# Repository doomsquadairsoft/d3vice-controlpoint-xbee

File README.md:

# d3vice-controlpoint-xbee
Arduino Fio / XBee based D3VICE control point for Airsoft games

## Feedback

If you have used and enjoy this code base, I'd love to hear from you!

## Development setup process

  * Download, Install [Atom editor](https://atom.io)
  * Download, Install [Platformio](https://platformio.org/install/ide?install=atom) Atom package
  * Restart atom. Open Atom & PlatformIO then import this repo.

??? @TODO once I figure out the process after this
  * Install contributed libraries `Sketch > Include Libraries > Manage Libraries`
    * Adafruit NeoPixel library
    * XBee-Arduino library
  * Add your user account to tty and dialout groups (May or may not be required for your OS)
    * `sudo usermod -aG tty,dialout <YOUR_USERNAME_HERE>`

## Enclosure Ideas

  * [MTM Survivor Dry Box with O-Ring Seal, Large](https://www.amazon.com/MTM-Survivor-Ring-Orange-Large/dp/B002KENWZY/ref=pd_rhf_ee_s_cp_0_3?_encoding=UTF8&pd_rd_i=B002KENWZY&pd_rd_r=DREY47809SR4JA75TENW&pd_rd_w=tL9qp&pd_rd_wg=YghNF&psc=1&refRID=DREY47809SR4JA75TENW)
  * [Seahorse SE-300 Protective Case Without Foam](https://www.amazon.com/Seahorse-Protective-Case-without-Orange/dp/B001A1TR1Q/ref=sr_1_14?ie=UTF8&qid=1509563510&sr=8-14&keywords=waterproof+case)

## XBee

### Setup

To connect to the XBee, a [SparkFun FTDI Basic Breakout 3.3v](https://www.sparkfun.com/products/9873) is used along with an [Adafruit XBee Adapter kit v1.1](https://www.adafruit.com/product/126). As my Adafruit XBee adapter kit v1.1 is discontinued, the replacment seems to be Adafruit's [USB XBee Adapter](https://www.adafruit.com/product/247) which I haven't tested but should do the trick. A separate FTDI chip isn't necessary with that new model.

XCTU is the program for configuring XBee modules. It is cross-platform.

57600 baudrate

Set the controlpoint as an ZB Router API NOT a ZB Endpoint API! Endpoint will work, but has complications with sleep mode.

#### XCTU Troubleshootinghttps://www.youtube.com/watch?v=ChCHfJoo9CQ

Make sure if using it on linux, you add yourself to the `dialout` group. Example: `sudo usermod -a -G dialout chris`

Make sure Arduino IDE is closed when working with XCTU. Radio discovery can be finnicky, but it works when it works.

XCTU's download links on Digi's website are usually broken. Find the filename from the [download page](https://www.digi.com/products/xbee-rf-solutions/xctu-software/xctu#productsupport-drivers), then manually browse their [ftp server](ftp://ftp1.digi.com/support/utilities/) for the correct version of XCTU.

If you can't get XCTU to communicate with your XBee, the rule of thumb is keep trying. It doesn't always work the first or second time. Try the different connection methods as well, from discovery to manually entering XBee serial/USB configuration.

### Power

The XBee is very sensitive when it comes to power. It needs as close to 3.3V as possible. When using USB, the Fio gives it a clean 3.285V. 3.296 was acheived using the buck converter regulator and that seemed to do the trick. If you are attempting to remotely program the XBee using X-CTU, and the read process seems slow, it may be that the XBee is crashing when it tries to pull power. Check voltages and try again.

### IDs

#### PAN ID

0x73706F6B616E6561 (ASCII spokanea)

#### switzerland-robust

SH 0013A200
SL 40B51A26

#### borders-portals

SH 0013A200
SL 40B774EC

## Special Thanks

The following people have helped this project in some way, and deserve a mention. Thank you all for helping this project become a reality!

  * [BulldogLowell](https://forum.arduino.cc/index.php?action=profile;u=258955) for helping me with code when I got stuck
  * [gfvalvo](https://forum.arduino.cc/index.php?action=profile;u=557197) for helping me with code when I got stuck
  * [Jiggy-Ninja](https://forum.arduino.cc/index.php?action=profile;u=53253) a.k.a. [MarkRD](https://hackaday.io/MarkRD) for helping me with code when I got stuck

## Todo list

  * [x] Fix phase 3 issue where ttw is ???
  * [ ] Implement XBee
  * [ ] Implement debugging via XBee wireless link
  * [x] Fix button debounce issue
  * [x] Fix endless beep on phase >=1
  * [x] Add button hold logic
  * [x] Implement ButtonManager
  * [ ] Try LoRa radio [Moteino](https://lowpowerlab.com/shop/product/119) looks nice.

## Parts list

  * (2) 220 Ohm resistor (JP3 button LEDs) DEPRECATED -- The buttons have their own capacitor
  * (3) 10K Ohm resistor (x2 JP4 button switches, x1 Battery Voltage Divider)
  * (1) 100K Ohm resistor (Battery voltage divider)
  * (1) 470 Ohm resistor (R1 Level shifter)
  * (1) 100 Ohm resistor (R2 buzzer)
  * (1) [Arduino Fio](https://amzn.to/2vkoAoj)
  * (1) 900MHz series XBee S2B
  * (1) [Digi JF1R6-CR3-4I U.FL fem to RPSMA fem cable](https://www.mouser.com/productdetail/digi-international/jf1r6-cr3-4i?qs=YPg7lQ8MWSd%252bJ21AYb5tjA%3D%3D)
  * (1) [2.4GHz dipole antenna](https://www.mouser.com/ProductDetail/Laird-LS-Research/001-0001?qs=%2fha2pyFaduic7%252bgB%2fLd2y%2fydYaVrig4l0IiQcO85%252biN2Plogftrjhg%3d%3d) (@TODO this doesn't seem right)
  * (1) 5V Buzzer
  * (1) 1000 uF electrolytic capacitor
  * (1) [TI 74AHCT125](http://adafru.it/1787) (NeoPixel 3V to 5V level shifter)
  * (1) [Red Arcade pushbutton](https://amzn.to/2qzc0vI)
  * (1) [Blue Arcade pushbutton](https://amzn.to/2vszEjp)
  * (2) [18650 Cell holder](https://amzn.to/2JN0Lsh)
  * (2) 18650 Li-Ion 3.7V battery
  * (1) [Qunqi MP1584EN DC-DC Buck Converter](https://amzn.to/2EPh9oB)
    * (1) [Alternative Power supply 001](https://www.ebay.com/itm/Durable-Quality-DC-DC-12V-To-3-3V-5V-Buck-Step-down-Power-Supply-Module-RH/113014911452?hash=item1a5036b1dc:g:4ecAAOSwzWpZjrM5)
  * (1) [MTM Survivor Dry Box with O-Ring](https://amzn.to/2JQuaSx)
  * (1) [Medium keyswitch](https://www.sparkfun.com/products/retired/11473)
  * (n) [24 AWG copper wire](https://amzn.to/2FrzB6S)
  * (2) [Chasis handles](https://www.mouser.com/ProductDetail/RAF-Electronic-Hardware/8075-440-A-24?qs=%2fha2pyFadugv9UkFwjFj1mse%2fGe0gQVLL5igE44%2fsfXi69vVZQTh6A%3d%3d)
  * (?) [4-40 bolts](https://www.banggood.com/4-40-UNC-Stainless-Steel-Hex-Socket-Head-Cap-Screws-Nuts-Assortment-Kit-126pcs-p-1147256.html?rmmds=search&cur_warehouse=CN)
  * (?) [LED Strip Housing](https://www.ebay.com/itm/50cm-U-V-YW-Aluminium-Housing-Holder-For-LED-Strip-Light-Bar-Under-Cabinet-Lamp/372358319157?hash=item56b2490c35:m:mi8XunysgHwlc1OMXDJ0slw:rk:29:pf:0)
  * (2) [Arcade Button Quick-Connect Wire Pairs - 0.11"](https://www.adafruit.com/product/1152)

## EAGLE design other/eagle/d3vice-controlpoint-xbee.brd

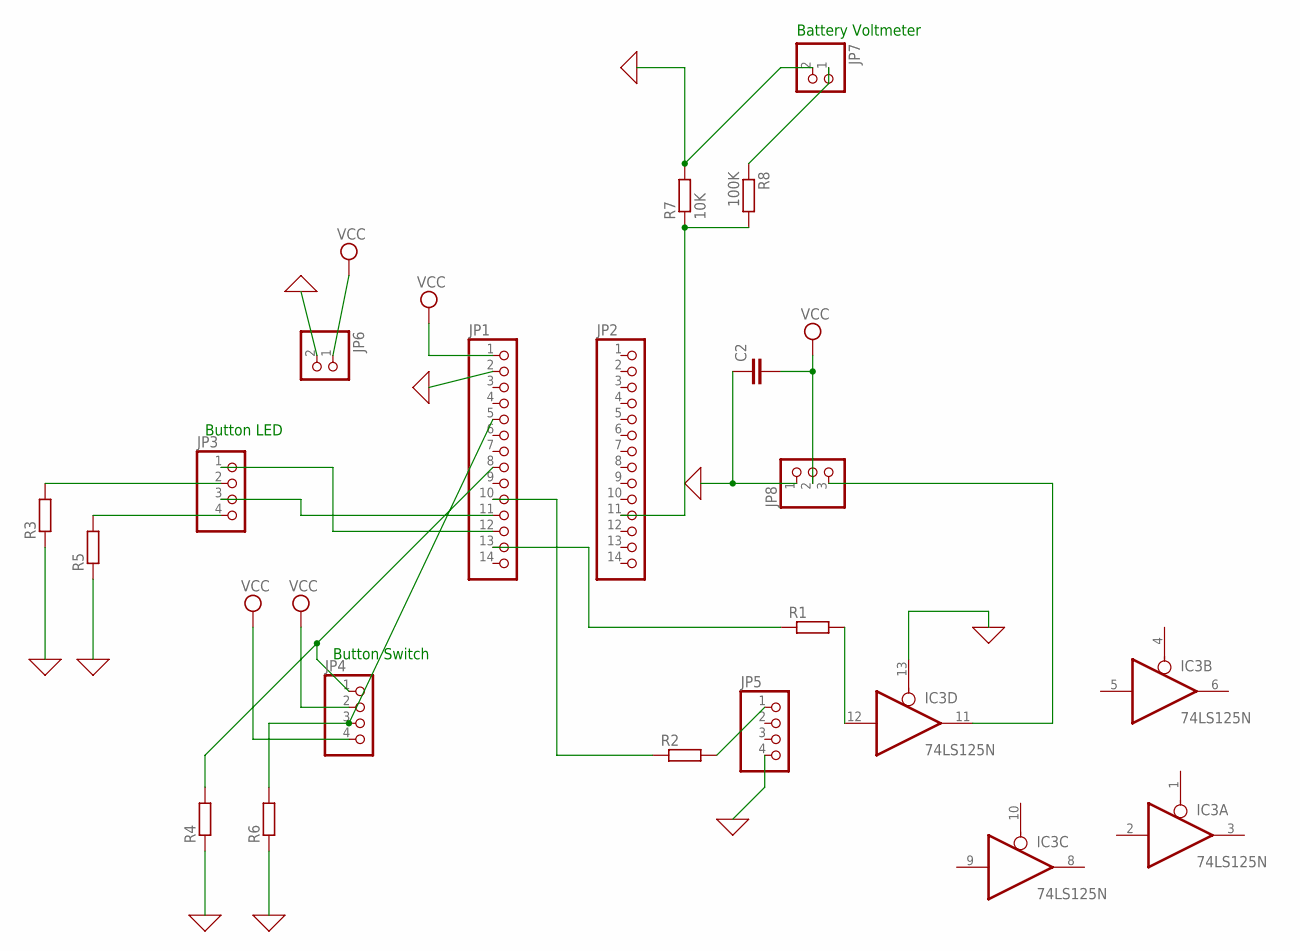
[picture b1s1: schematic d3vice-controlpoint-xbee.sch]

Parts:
C2: C-EU050-045X075; C050-045X075
IC3: 74LS125N; DIL14
JP1, JP2: PINHD-1X14; 1X14
JP3, JP4, JP5: PINHD-1X4; 1X04
JP6, JP7: PINHD-1X2; 1X02
JP8: PINHD-1X3; 1X03
R1, R2, R3, R4, R5, R6: R0204/7; 0204/7
R7: 10K; 0204/7
R8: 100K; 0204/7

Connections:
0: JP7.2, R7.2
GND: C2.1, IC3.7 (GND), IC3.13 (OE), JP1.2, JP5.4, JP6.2, JP8.1, R3.1, R4.1, R5.1, R6.1
unnamed: JP2.11, R7.1, R8.2
unnamed: IC3.11 (O), JP8.3
unnamed: IC3.12 (I), R1.2
unnamed: JP5.1, R2.2
unnamed: JP1.5, JP4.3, R6.2
unnamed: JP1.13, R1.1
unnamed: JP1.10, R2.1
unnamed: JP1.11, JP3.3
unnamed: JP3.4, R5.2
unnamed: JP3.2, R3.2
unnamed: JP1.12, JP3.1
unnamed: JP7.1, R8.1
unnamed: JP1.8, JP4.1, R4.2
VCC: C2.2, IC3.14 (VCC), JP1.1, JP4.2, JP4.4, JP6.1, JP8.2

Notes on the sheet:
Button LED
Button Switch
Battery Voltmeter

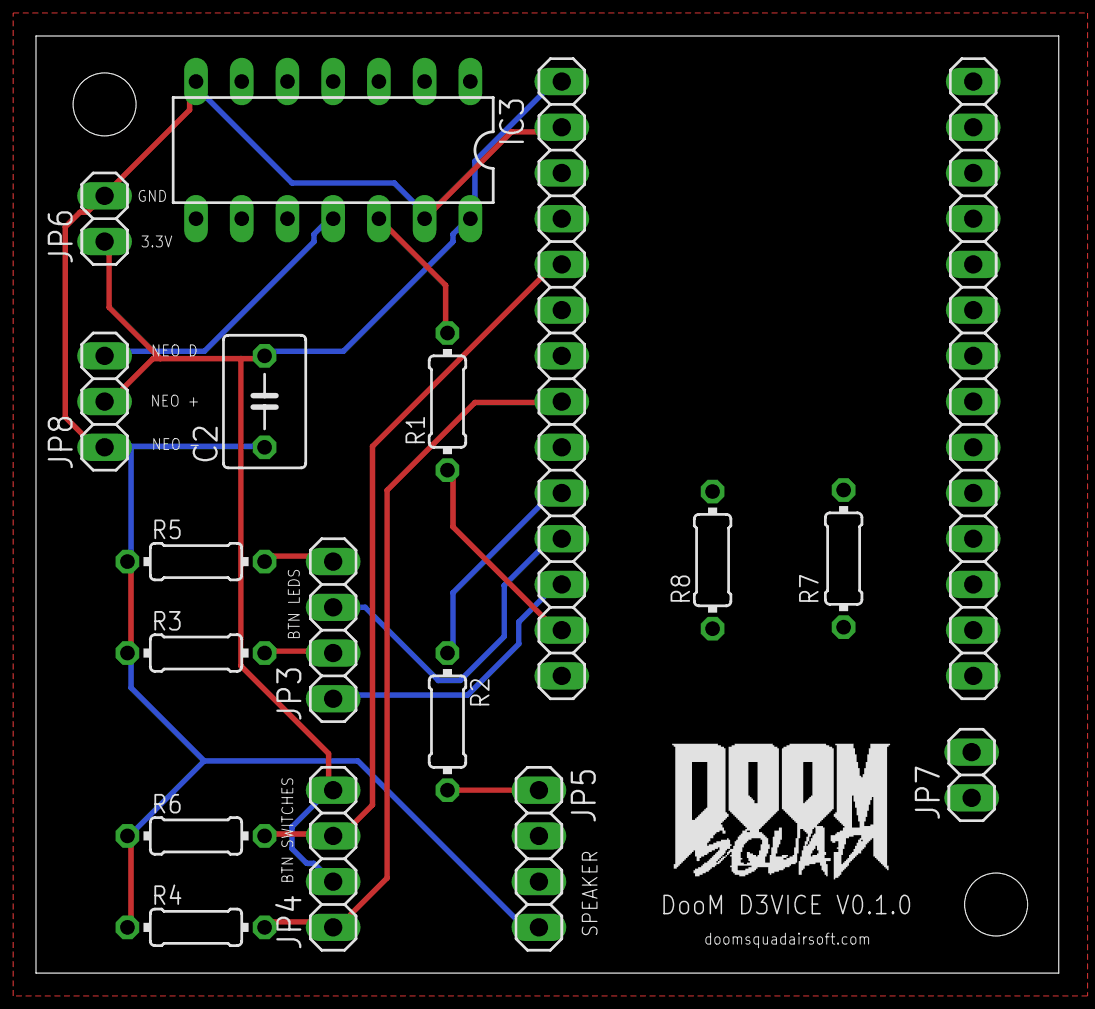
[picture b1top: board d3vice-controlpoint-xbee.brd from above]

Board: 2 copper layers, 56.8 x 52.1 mm, 18 parts (0 on the bottom side), 16 nets.

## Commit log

2017-12-02 adding classes
2017-12-02 my idea compiles!
2017-12-02 more prototyping
2017-12-03 progress
2017-12-03 implement buzzer
2017-12-04 button LEDs implemented
2017-12-05 add default yellw breather animation
2017-12-05 implement strobing effect after button presses
2018-01-22 proress
2018-01-22 remove Event class, reduce complexity
2018-01-23 add phase specifications
2018-01-23 add Phase class
2018-01-23 asyncBeep and asyncMorse scaffoldiing
2018-01-24 refactor for Controller class
2018-01-24 refactor for Controller with pointers
2018-01-24 add pretty hyperlink
2018-01-24 fix formatting
2018-01-24 fix usermod incantation
2018-01-25 update LightStrip for phases
2018-01-25 add Radio class
2018-01-26 add saythanks button
2018-01-26 debugging phase advancement
2018-01-26 debugging button debouncing
2018-01-26 add todo list
2018-01-27 fix button debounce issue
2018-01-27 debugging sound module
2018-01-28 fix endless buzzer bug
2018-01-28 remove debug delays and speed up test seq
2018-01-29 add scaffolding for ButtonManager & multi-button holds
2018-01-31 fixing ButtonManager reference issue
2018-01-31 add notes about helpers
2018-01-31 add labels
2018-01-31 update todo
2018-01-31 fix positioning
2018-02-11 debugging phase3 button presses and ttw
2018-02-12 im stuck. Button _teamNumber is misbehaving
2018-02-23 fix button bug where both buttons had same teamNumber
2018-03-04 switch to references
2018-03-04 remove Controller
2018-03-04 remove remnants of Controller
2018-03-10 refactor for working phase management
2018-03-11 Fix rapid-fire phase advancement bug
2018-03-11 add Phase2 selection, implement holdRelease bug
2018-03-12 filling in the menu
2018-03-13 add config class in favor of identical but different named config classes
2018-03-13 remove note about unused paradigm
2018-04-14 commit before major refactor
2018-04-14 refactor
2018-04-20 add parts list
2018-05-04 add cad files
2018-05-08 add pics and vids
2018-05-08 trim heatissue clip
2018-05-08 rotate vid, add pcb pics
2018-07-29 non-melty communication established
2018-07-30 add standby strobe
2018-08-02 add notes about mk1
2018-08-02 mk1 measurement notes
2018-08-02 handle specs
2018-08-05 aug31-demo
2018-08-06 incomplete progress bar implementation
2018-08-06 progress bar partial implementation
2018-08-07 implemented basic progressbar
2018-11-04 add mounting holes
2019-02-13 convert to PlatformIO project
2019-02-13 add travis file and example test
2019-02-23 added battery voltage circuit
2019-02-23 add battery testing phase
2019-02-23 add fio schematic
2019-02-23 update docs
2019-02-26 update phase names
2019-02-26 switch to JC_Button library
2019-02-27 fix phase switching bug
2019-03-03 fix progress bar... almost
